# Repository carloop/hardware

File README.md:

# [Carloop](https://www.carloop.io)
## OBD-II CAN adapter for the Particle Photon/Electron and RedBear Duo

The WiFi-capable Particle Photon or better yet the cellular Particle
Electron can turn your car into a cloud connected device!

Carloop's PCB connects your car's CAN bus network to the Photon, Electron and Duo. It also provides battery power and a GPS to track location.

# Particle Photon Example

# [Check out the Carloop Store](https://store.carloop.io/)

## Features

* High-speed CAN transceiver [adapted from the OpenXC project](https://github.com/openxc/reference-vi/blob/gh-pages/electrical/design/can.mkd)
* Get power from the OBD-II port using [a robust circuit adapted from the OpenXC project](https://github.com/openxc/reference-vi/blob/gh-pages/electrical/design/power.mkd)
* GPS connector
* Stacked components for a more compact development kit than a
traditional 90-degrees PCB mount OBD-II connector.
* Powered by the Particle platform!

## Images

PCB

Assembled adapter

* [With Photon](images/detail-photon.jpg)
* [With Electron](images/detail-electron.jpg)
* [Front view](images/front.png)
* [Side view](images/detail-side.jpg)
* [Back view](images/back.png)
* [Angle view](images/angle.png)

## Hardware

There are a few hardware variants: [Carloop](Carloop.v2), [Carloop XL](CarloopXL.v3) and [Carloop Retro](CarloopRetro.v0).

Here are the PCB design files for the Revision 2.3, the one sold on the [Carloop store](https://store.carloop.io)

* [Schematic (PDF)](Carloop.v2/Carloop-v2.3.pdf)
  [(Eagle)](Carloop.v2/Carloop-v2.3.sch)
* [Layout](Carloop.v2/Carloop-v2.3-pcb-combined.pdf)
  [(top)](Carloop.v2/Carloop-v2.3-layout-top.pdf)
  [(bottom)](Carloop.v2/Carloop-v2.3-layout-bottom.pdf)
  [(Eagle)](Carloop.v2/Carloop-v2.3.brd)
* [Bill of materials](Carloop.v2/Carloop-v2.3_BOM.csv)
* [OSH Park order page](https://oshpark.com/shared_projects/ir8I9vT6)

Here are the PCB design files for the extended version that fits a Particle Electron. It is a prototype.

* [Schematic (Eagle)](CarloopXL.v3/Carloop-v3.1.sch)
* [Layout (Eagle)](CarloopXL.v3/Carloop-v3.1.brd)
* [Bill of materials](CarloopXL.v3/Carloop-v3.1_BOM.csv)

Here are the PCB design files for a "retro" variant with a K-Line transceiver contributed by [Alan R](https://github.com/cyclin-al).

* [Schematic (Eagle)](CarloopRetro.v0/CarloopRetro-v0.1.sch)
* [Layout (Eagle)](CarloopRetro.v0/CarloopRetro-v0.1.brd)

## Software

The [Carloop Library](https://github.com/carloop/carloop-library) is available on Particle's Web IDE.  You will need to flash a [Particle Photon](https://store.carloop.io/products/particle-photon), [Particle Electron](https://store.carloop.io/products/particle-electron) or [RedBear Duo](https://store.carloop.io/products/redbear-duo) with an example app which can ben found in Carloop Library.   See 'Getting Started' instructions here: [https://community.carloop.io/t/getting-started-with-carloop/23](https://community.carloop.io/t/getting-started-with-carloop/23)

## License

Copyright 2016 1000 Tools, Inc.

Licensed under the GPL v3

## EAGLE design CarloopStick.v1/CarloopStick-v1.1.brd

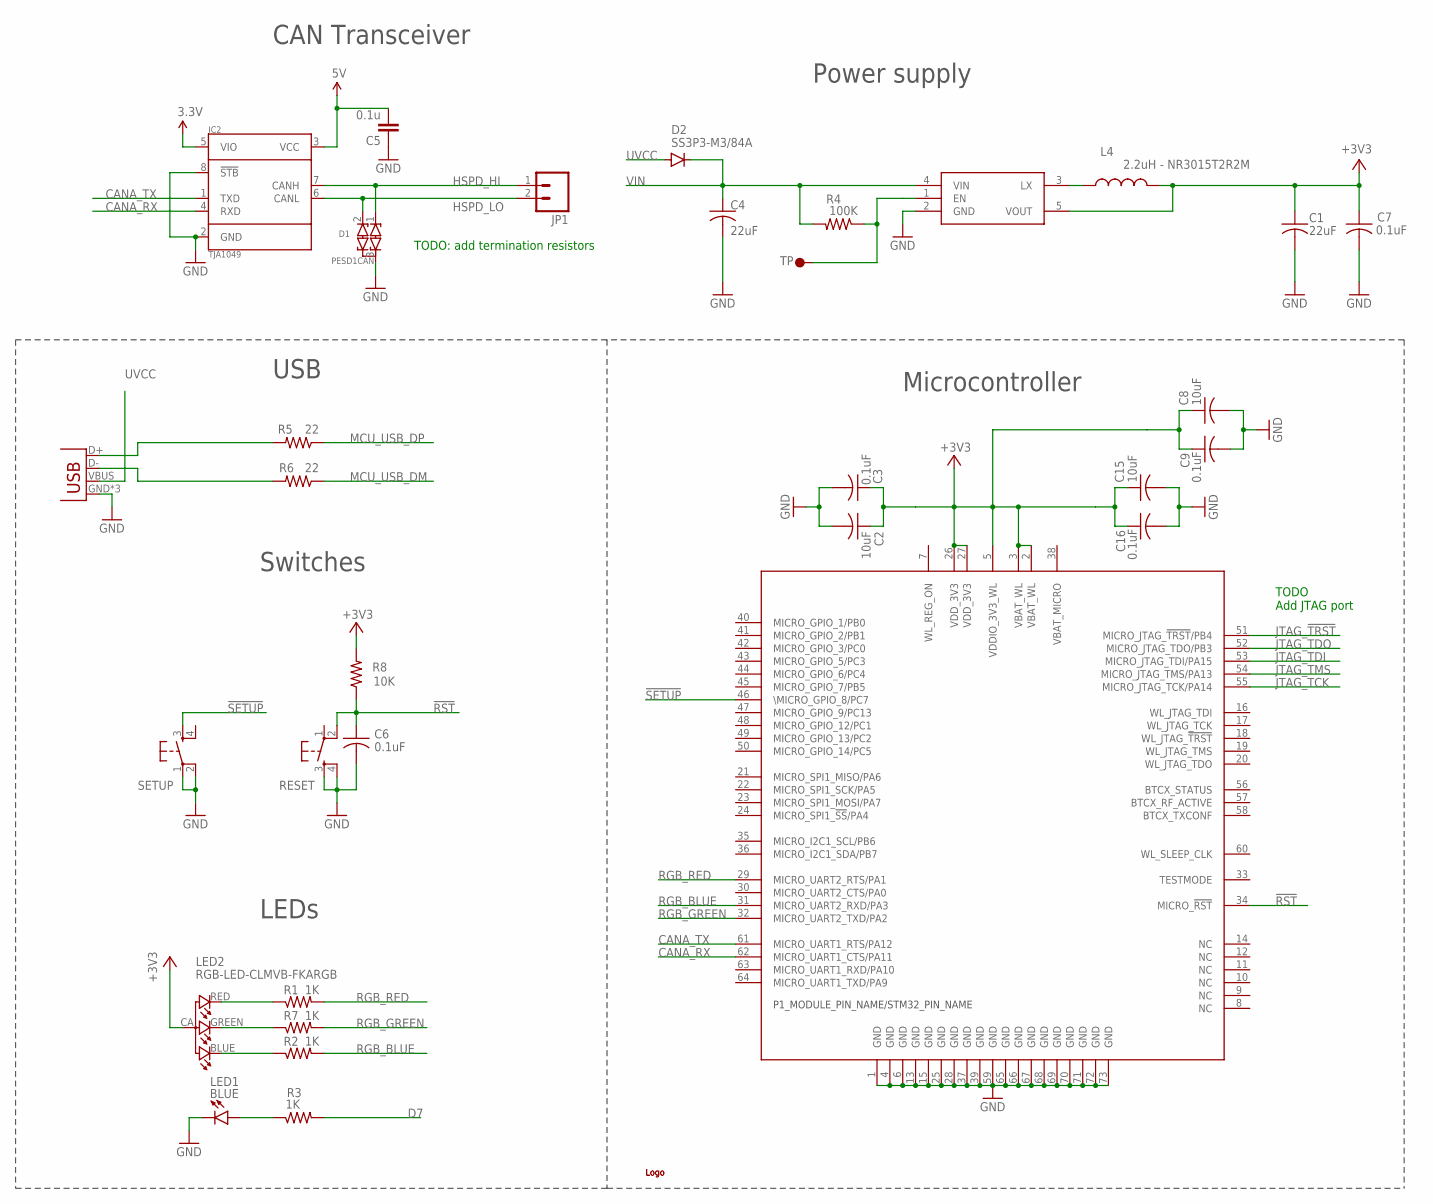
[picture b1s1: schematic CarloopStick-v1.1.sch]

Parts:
C1, C4: 22uF; C0603_B
C2, C8, C15: 10uF; C0603_B
C3, C6, C7, C9, C16: 0.1uF; C0402_B
C5: 0.1u; C0402; PARTNO GRM155R71C104KA88D
D1: PESD1CAN; SOT23; PARTNO PESD1CAN-215
D2: SS3P3-M3/84A; DIODE-DO-220AA(SMP)
IC2: TJA1049; SO8; PARTNO TJA1049T-118
JP1: M02PTH; 1X02
L4: 2.2uH - NR3015T2R2M; INDUCTOR-NR3015
LED2: RGB-LED-CLMVB-FKARGB; PLCC4-2MM-RGB
LED_USR: BLUE; LED-0603-NO-SS
R1, R2, R3, R7: 1K; R0402_B
R4: 100K; R0402_B
R5, R6: 22; R0402_B
R8: 10K; R0402_B
RESET: KMR211GLFS; TACTILE_SWITCH_SMD
SETUP: KMR211GLFS; TACTILE_SWITCH_SMD
U$1, U$5: LOGOSMALL; CARLOOP-2
U$4: P1; WM-N-BM-14
U$11: R8008-33; SOT23-5
U$12: TP3; TP60_BOT
X1: USB-MICROB; USB-MICROB-SLOT-HOLE

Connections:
3.3V: IC2.5 (VIO)
5V: C5.2, IC2.3 (VCC)
!RST: C6.1, R8.1, RESET.2, U$4.34 (MICRO_!RST!)
!SETUP: SETUP.3, U$4.46 (\MICRO_GPIO_8/PC7)
+3V3: C1.1, C2.1, C3.1, C7.1, C8.1, C9.1, C15.1, C16.1, L4.2, LED2.CA (1), R8.2, U$4.2 (VBAT_WL), U$4.3 (VBAT_WL), U$4.5 (VDDIO_3V3_WL), U$4.26 (VDD_3V3), U$4.27 (VDD_3V3), U$11.5 (VOUT)
CANA_RX: IC2.4 (RXD), U$4.62 (MICRO_UART1_CTS/PA11)
CANA_TX: IC2.1 (TXD), U$4.61 (MICRO_UART1_RTS/PA12)
D7: R3.2
GND: C1.2, C2.2, C3.2, C4.2, C5.1, C6.2, C7.2, C8.2, C9.2, C15.2, C16.2, D1.3 (COM), IC2.2 (GND), IC2.8 (!STB), LED_USR.C1 (C), RESET.3, RESET.4, SETUP.1, SETUP.2, U$4.1 (GND), U$4.4 (GND), U$4.6 (GND), U$4.13 (GND), U$4.15 (GND), U$4.25 (GND), U$4.28 (GND), U$4.37 (GND), U$4.39 (GND), U$4.59 (GND), U$4.65 (GND), U$4.66 (GND), U$4.67 (GND), U$4.68 (GND), U$4.69 (GND), U$4.70 (GND), U$4.71 (GND), U$4.72 (GND), U$4.73 (GND), U$11.2 (GND), X1.GND, X1.MT1 (GND), X1.MT2 (GND)
HSPD_HI: D1.1 (C1), IC2.7 (CANH), JP1.1
HSPD_LO: D1.2 (C2), IC2.6 (CANL), JP1.2
JTAG_!TRST: U$4.51 (MICRO_JTAG_!TRST!/PB4)
JTAG_TCK: U$4.55 (MICRO_JTAG_TCK/PA14)
JTAG_TDI: U$4.53 (MICRO_JTAG_TDI/PA15)
JTAG_TDO: U$4.52 (MICRO_JTAG_TDO/PB3)
JTAG_TMS: U$4.54 (MICRO_JTAG_TMS/PA13)
LED1: LED_USR.A1 (A), R3.1
MCU_USB_DM: R6.1
MCU_USB_DP: R5.1
unnamed: R5.2, X1.D+
unnamed: L4.1, U$11.3 (LX)
unnamed: R6.2, X1.D-
unnamed: R4.1, U$11.1 (EN), U$12.P$1
unnamed: LED2.BLUE (2), R2.1
unnamed: LED2.GREEN (3), R7.1
unnamed: LED2.RED (4), R1.1
RGB_BLUE: R2.2, U$4.31 (MICRO_UART2_RXD/PA3)
RGB_GREEN: R7.2, U$4.32 (MICRO_UART2_TXD/PA2)
RGB_RED: R1.2, U$4.29 (MICRO_UART2_RTS/PA1)
UVCC: D2.ANODE, X1.VBUS
VIN: C4.1, D2.CATHODE, R4.2, U$11.4 (VIN)

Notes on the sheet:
CAN Transceiver
USB
Microcontroller
Power supply
Switches
LEDs
TODO Add JTAG port
TODO: add termination resistors

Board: 2 copper layers, 34 parts (0 on the bottom side), 22 nets, no tracks yet.

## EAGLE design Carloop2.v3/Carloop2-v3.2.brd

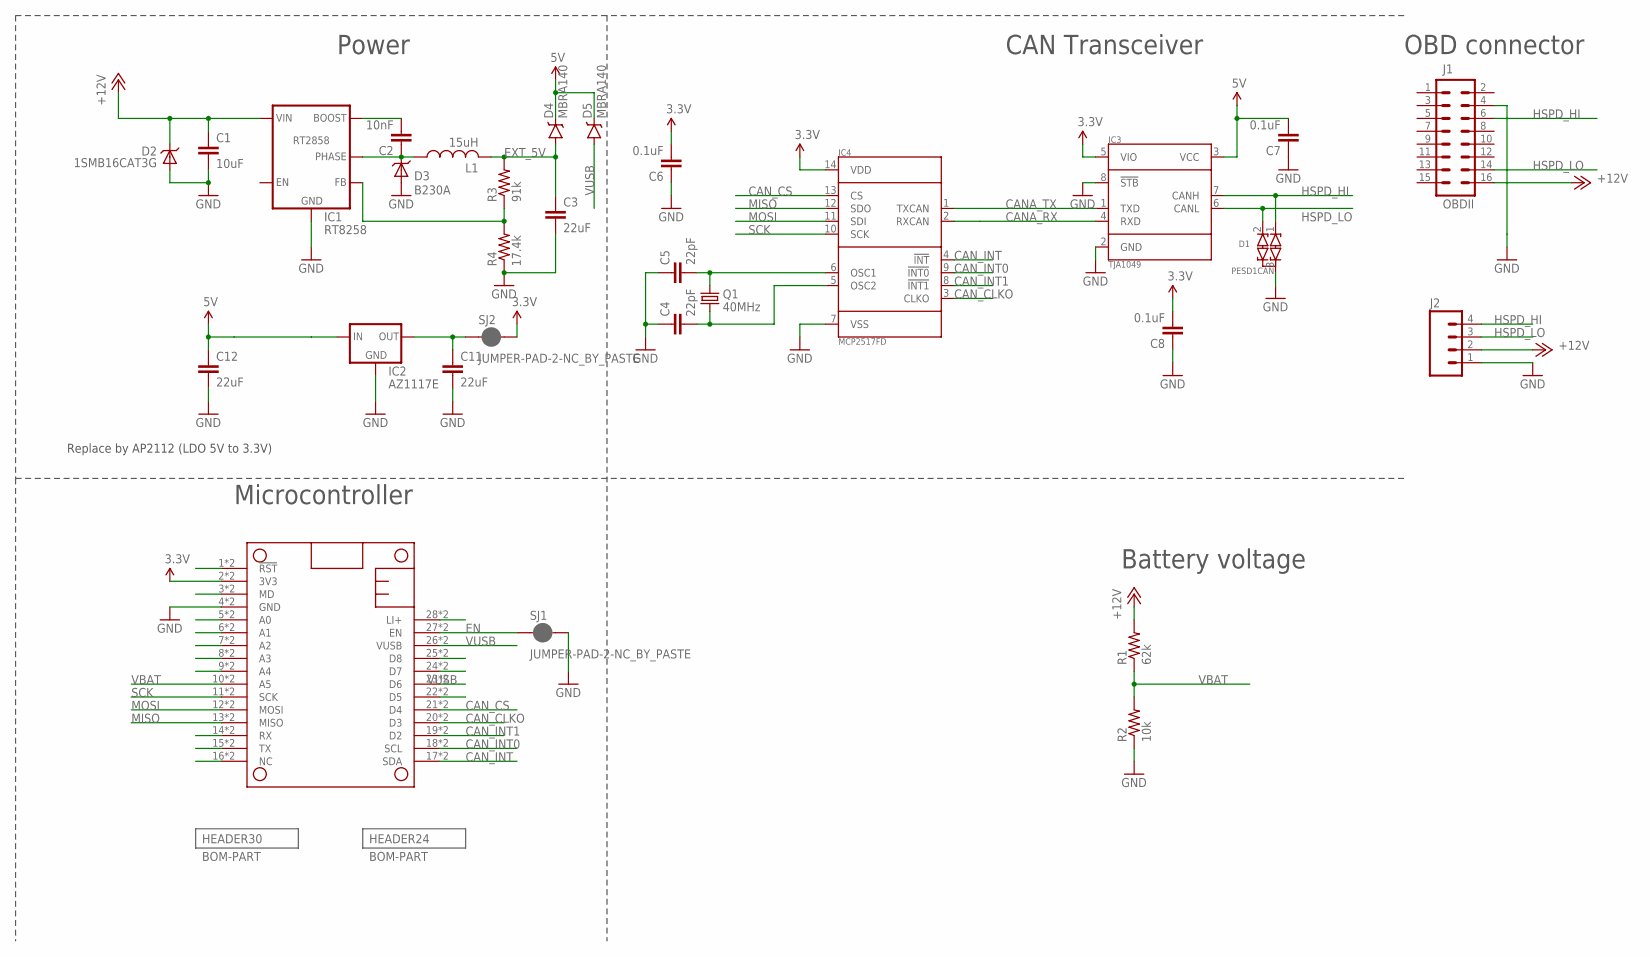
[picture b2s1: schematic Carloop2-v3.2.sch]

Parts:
C1: 10uF; C1206; PARTNO C3216X7R1E106K160AB
C2: 10nF; C0603; PARTNO CGA3E2X8R1H103K080AA
C3, C11, C12: 22uF; C1206; PARTNO CL31X226KAHN3NE
C4, C5: 22pF; C0603; PARTNO CC0603KRX7R9BB223
C6, C7, C8: 0.1uF; C0603; PARTNO CC0603JRX7R7BB104
D1: PESD1CAN; SOT23; PARTNO PESD1CAN-215
D2: 1SMB16CAT3G; SMB-DIODE; PARTNO 1SMB16CAT3G
D3: B230A; DO-214AA; PARTNO B230A-13-F
D4, D5: MBRA140; SMA-DIODE; PARTNO MBRA140T3G
IC1: RT8258; SOT-23-6; PARTNO RT8258GJ6
IC2: AZ1117E; SOT223; PARTNO AZ1117EH-3.3TRG1
IC3: TJA1049; SO8; PARTNO TJA1049T-118
IC4: MCP2517FD; SOIC-14; PARTNO MCP2517FD-H/SL
IC5: PARTICLE_MESH_SMTDUAL; FEATHERWING_SMT2
J1: OBDII; OBDII-COMTECH; PARTNO OBD-II
J2: M04SCREW; SCREWTERMINAL-3.5MM-4; PARTNO OSTTE040104
L1: 15uH; NR8040; PARTNO NR8040T150M
Q1: 40MHz; CRYSTAL-SMD-5X3; PARTNO ECS-400-12-30B-AGM-TR
R1: 62k; R0603; PARTNO ERA-3AEB623V
R2: 10k; R0603; PARTNO ERA-3AED103V
R3: 91k; R0603; PARTNO ERA-3ARB913V
R4: 17.4k; R0603; PARTNO ERJ-3EKF1742V
SJ1, SJ2: JUMPER-PAD-2-NC_BY_PASTE; PAD-JUMPER-2-NC_BY_PASTE_YES_SILK

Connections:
3.3V: C6.2, C8.2, IC3.5 (VIO), IC4.14 (VDD), IC5.2 (3V3), IC5.2' (3V3), SJ2.2
5V: C7.2, C12.1, D4.C, D5.C, IC2.3 (IN), IC3.3 (VCC)
+12V: C1.1, D2.C, IC1.5 (VIN), J1.16, J2.2, R1.2
BOOST\: C2.2, IC1.1 (BOOST)
CANA_RX: IC3.4 (RXD), IC4.2 (RXCAN)
CANA_TX: IC3.1 (TXD), IC4.1 (TXCAN)
CAN_CLKO: IC4.3 (CLKO), IC5.20 (D3), IC5.20' (D3)
CAN_CS: IC4.13 (CS), IC5.21 (D4), IC5.21' (D4)
CAN_INT: IC4.4 (!INT), IC5.17 (SDA), IC5.17' (SDA)
CAN_INT0: IC4.9 (!INT0), IC5.18 (SCL), IC5.18' (SCL)
CAN_INT1: IC4.8 (!INT1), IC5.19 (D2), IC5.19' (D2)
EN: IC5.27 (EN), IC5.27' (EN), SJ1.1
EXT_5V: C3.1, D4.A, L1.P$2 (2), R3.2
FB: IC1.3 (FB), R3.1, R4.2
GND: C1.2, C3.2, C4.1, C5.1, C6.1, C7.1, C8.1, C11.2, C12.2, D1.3 (COM), D2.A, D3.+ (A), IC1.2 (GND), IC2.1 (GND), IC2.4 (GND), IC3.2 (GND), IC3.8 (!STB), IC4.7 (VSS), IC5.4 (GND), IC5.4' (GND), J1.4, J2.1, R2.1, R4.1, SJ1.2
HSPD_HI: D1.1 (C1), IC3.7 (CANH), J1.6, J2.4
HSPD_LO: D1.2 (C2), IC3.6 (CANL), J1.14, J2.3
LI+: IC5.28 (LI+), IC5.28' (LI+)
MISO: IC4.12 (SDO), IC5.13 (MISO), IC5.13' (MISO)
MOSI: IC4.11 (SDI), IC5.12 (MOSI), IC5.12' (MOSI)
unnamed: C11.1, IC2.2 (OUT), SJ2.1
unnamed: C5.2, IC4.6 (OSC1), Q1.3 (2)
unnamed: IC5.1 (!RST), IC5.1' (!RST)
unnamed: IC5.3 (MD), IC5.3' (MD)
unnamed: IC5.5 (A0), IC5.5' (A0)
unnamed: IC5.6 (A1), IC5.6' (A1)
unnamed: IC5.7 (A2), IC5.7' (A2)
unnamed: IC5.8 (A3), IC5.8' (A3)
unnamed: IC5.9 (A4), IC5.9' (A4)
unnamed: IC5.25 (D8), IC5.25' (D8)
unnamed: IC5.24 (D7), IC5.24' (D7)
unnamed: IC5.23 (D6), IC5.23' (D6)
unnamed: IC5.22 (D5), IC5.22' (D5)
unnamed: IC5.14 (RX), IC5.14' (RX)
unnamed: IC5.15 (TX), IC5.15' (TX)
unnamed: IC5.16 (NC), IC5.16' (NC)
unnamed: C4.2, IC4.5 (OSC2), Q1.1
PHASE: C2.1, D3.- (C), IC1.6 (PHASE), L1.P$1 (1)
SCK: IC4.10 (SCK), IC5.11 (SCK), IC5.11' (SCK)
VBAT: IC5.10 (A5), IC5.10' (A5), R1.1, R2.2
VUSB: D5.A, IC5.26 (VUSB), IC5.26' (VUSB)

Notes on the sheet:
Power
Battery voltage
OBD connector
Microcontroller
CAN Transceiver
Replace by AP2112 (LDO 5V to 3.3V)

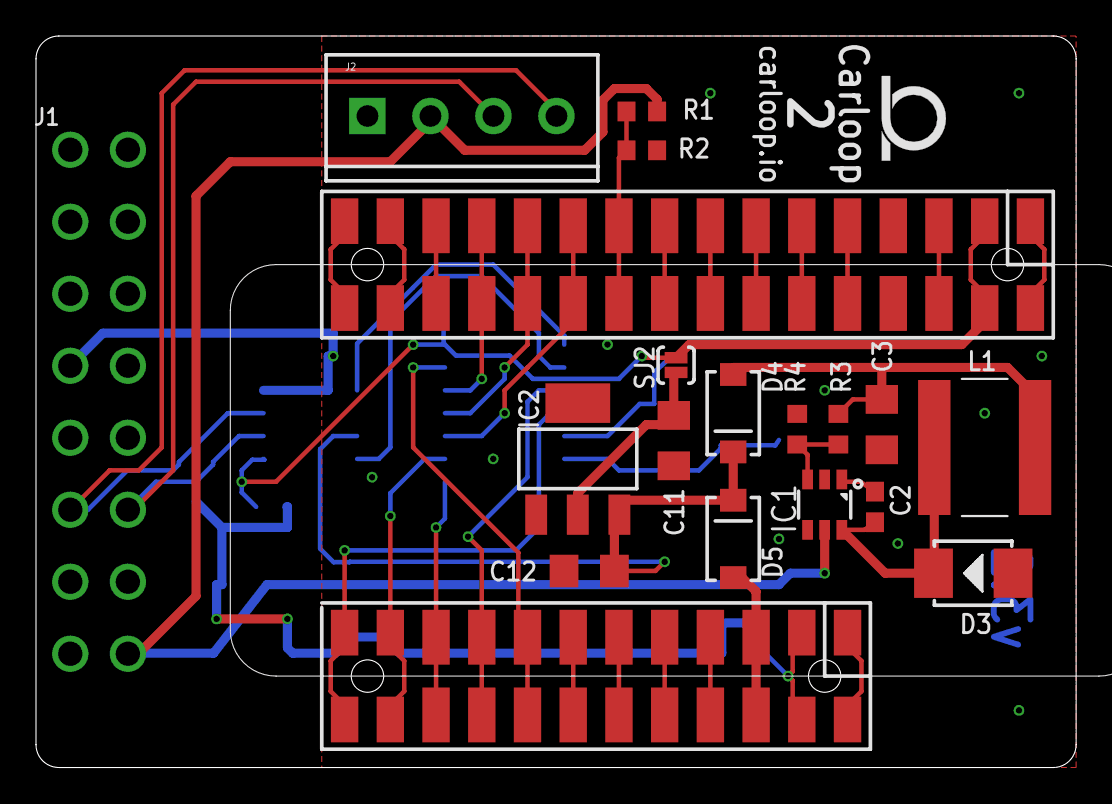
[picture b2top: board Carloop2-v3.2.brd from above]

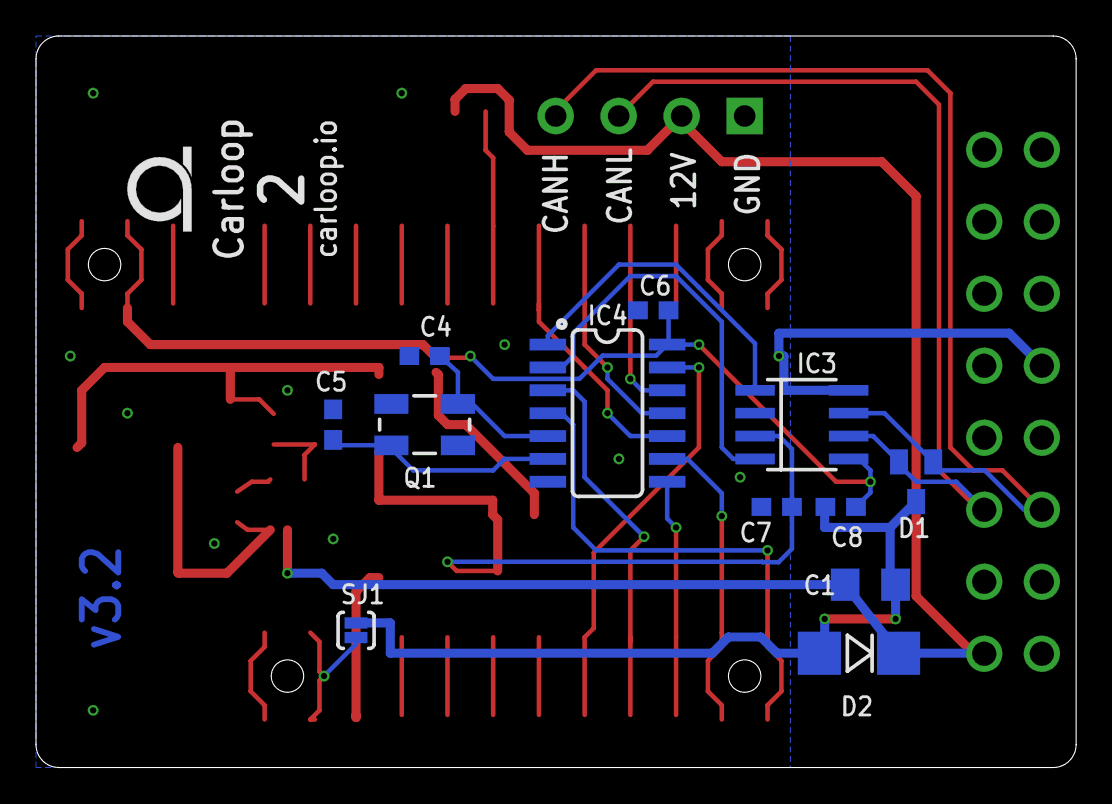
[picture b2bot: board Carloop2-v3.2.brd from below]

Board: 2 copper layers, 57.8 x 40.6 mm, 32 parts (13 on the bottom side), 41 nets.

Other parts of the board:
U$3, U$5: LOGOSMALL; CARLOOP-2

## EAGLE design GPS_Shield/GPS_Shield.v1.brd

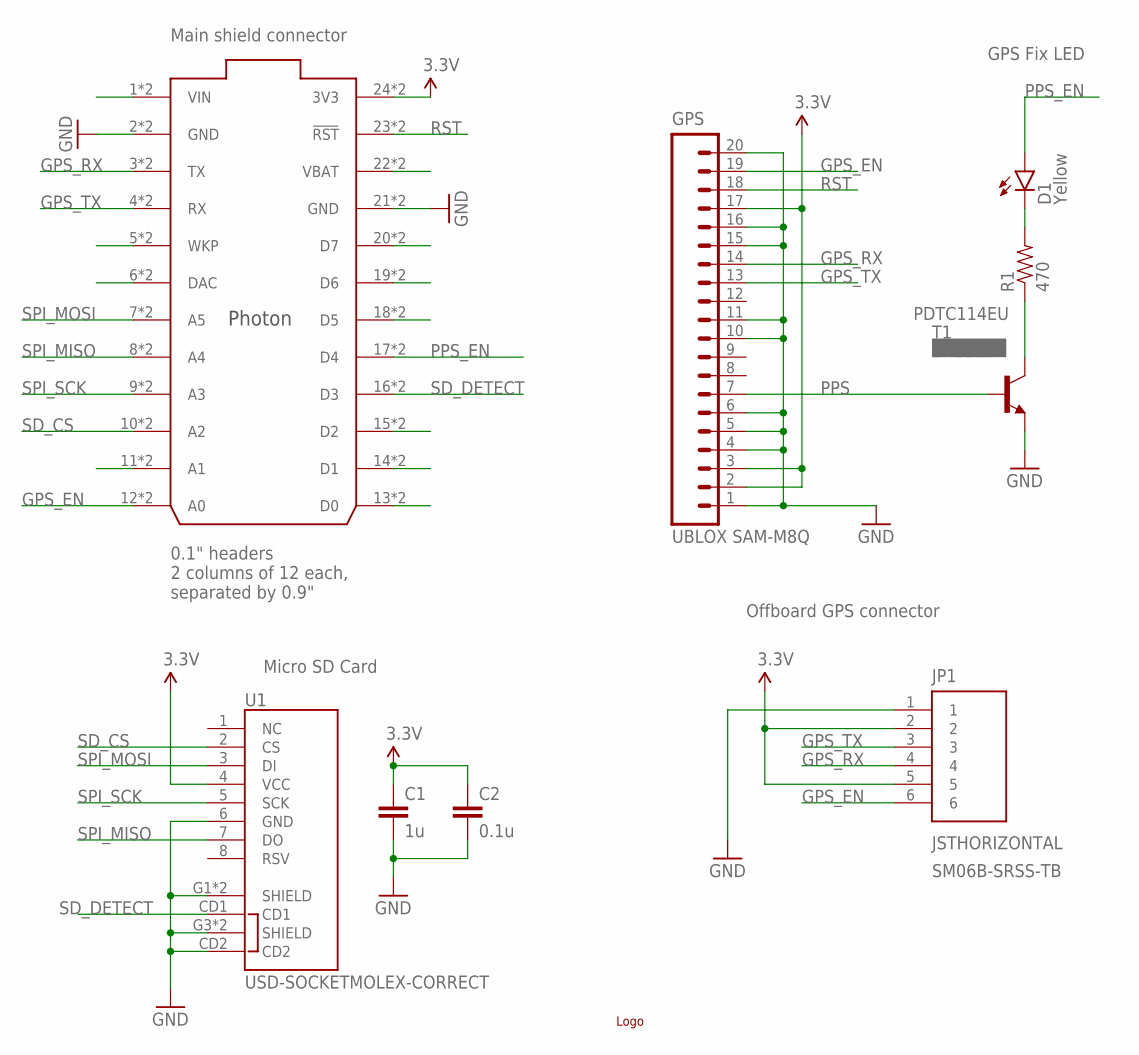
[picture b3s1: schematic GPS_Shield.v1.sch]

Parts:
C1: 1u; 0603-CAP
C2: 0.1u; 0603-CAP
CORE: PHOTONWITH_EXTERNAL_HEADERS; PHOTON_STACKABLE_EXTERNAL; PARTNO *
D1: Yellow; LED-0603
GPS: UBLOX SAM-M8Q; 1X20
JP1: JSTHORIZONTAL; JST-6-SMD-HOR-1.0MM; PARTNO SM06B-SRSS-TB
R1: 470; 0603-RES
T1: 2N2222; TO18
U1: USD-SOCKETMOLEX-CORRECT; MICRO-SD-MOLEX-CORRECT
U$1: LOGO; CARLOOP

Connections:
3.3V: C1.1, C2.1, CORE.24 (3V3), CORE.@24 (3V3), GPS.2, GPS.3, GPS.17, JP1.2, JP1.5, U1.4 (VCC)
CANA_EN: CORE.13 (D0), CORE.@13 (D0)
CANA_RX: CORE.15 (D2), CORE.@15 (D2)
CANA_TX: CORE.14 (D1), CORE.@14 (D1)
GND: C1.2, C2.2, CORE.2 (GND), CORE.21 (GND), CORE.@2 (GND), CORE.@21 (GND), GPS.1, GPS.4, GPS.5, GPS.6, GPS.10, GPS.11, GPS.15, GPS.16, GPS.20, JP1.1, T1.1 (E), U1.6 (GND), U1.CD2, U1.G1 (SHIELD), U1.G2 (SHIELD), U1.G3 (SHIELD), U1.G4 (SHIELD)
GPS_EN: CORE.12 (A0), CORE.@12 (A0), GPS.19, JP1.6
GPS_RX: CORE.3 (TX), CORE.@3 (TX), GPS.14, JP1.4
GPS_TX: CORE.4 (RX), CORE.@4 (RX), GPS.13, JP1.3
unnamed: R1.1, T1.3 (C)
unnamed: D1.C, R1.2
unnamed: CORE.6 (DAC), CORE.@6 (DAC)
unnamed: CORE.22 (VBAT), CORE.@22 (VBAT)
unnamed: CORE.20 (D7), CORE.@20 (D7)
unnamed: CORE.19 (D6), CORE.@19 (D6)
unnamed: CORE.1 (VIN), CORE.@1 (VIN)
unnamed: CORE.5 (WKP), CORE.@5 (WKP)
PPS: GPS.7, T1.2 (B)
PPS_EN: CORE.17 (D4), CORE.18 (D5), CORE.@17 (D4), CORE.@18 (D5), D1.A
RST: CORE.23 (!RST), CORE.@23 (!RST), GPS.18
SD_CS: CORE.10 (A2), CORE.@10 (A2), U1.2 (CS)
SD_DETECT: CORE.16 (D3), CORE.@16 (D3), U1.CD1
SPI_MISO: CORE.8 (A4), CORE.@8 (A4), U1.7 (DO)
SPI_MOSI: CORE.7 (A5), CORE.@7 (A5), U1.3 (DI)
SPI_SCK: CORE.9 (A3), CORE.@9 (A3), U1.5 (SCK)
VBAT: CORE.11 (A1), CORE.@11 (A1)

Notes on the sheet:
PDTC114EU
SM06B-SRSS-TB
Offboard GPS connector
0.1" headers 2 columns of 12 each, separated by 0.9"
Main shield connector
GPS Fix LED
Micro SD Card

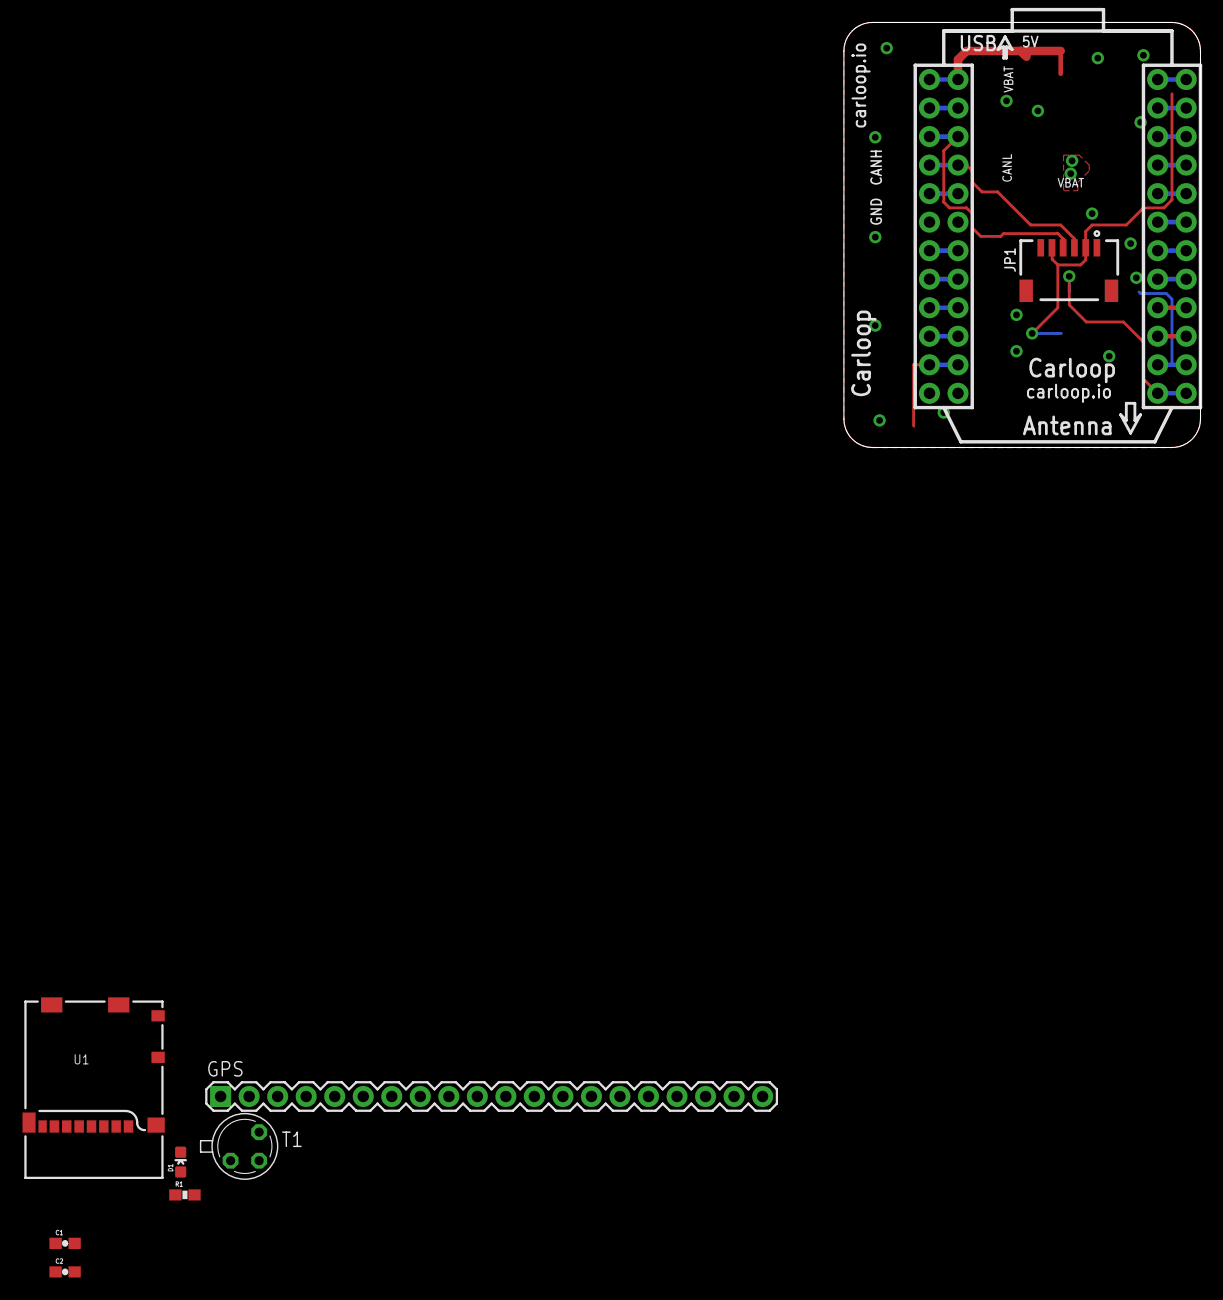
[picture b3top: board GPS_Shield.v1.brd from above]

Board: 2 copper layers, 31.8 x 37.8 mm, 12 parts (1 on the bottom side), 25 nets.

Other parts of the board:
F2: OSHW-LOGO-S
ZDRAW1: A4L-LOC

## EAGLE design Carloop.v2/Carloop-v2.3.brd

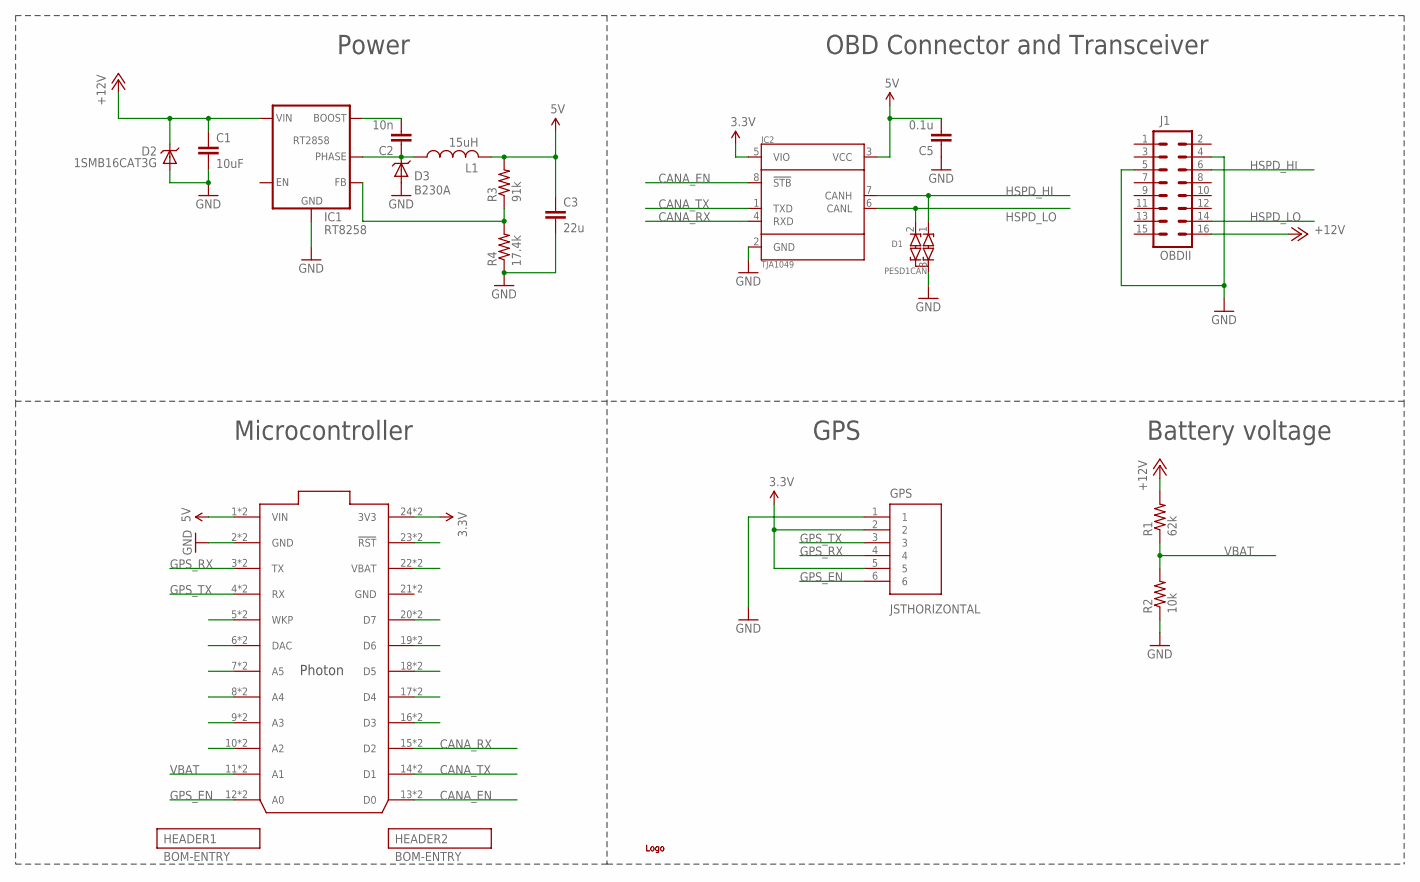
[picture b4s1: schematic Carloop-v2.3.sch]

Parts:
C1: 10uF; C1206; PARTNO GRM31CR61E106KA12L
C2: 10n; C0402; PARTNO C0402C103K5RACTU
C3: 22u; C1206; PARTNO GRM31CR61C226ME15L
C5: 0.1u; C0402; PARTNO GRM155R71C104KA88D
CORE: PHOTONWITH_EXTERNAL_HEADERS; PHOTON_STACKABLE_EXTERNAL; PARTNO *
D1: PESD1CAN; SOT23; PARTNO PESD1CAN-215
D2: 1SMB16CAT3G; SMB-DIODE; PARTNO 1SMB16CAT3G
D3: B230A; DO-214AA; PARTNO B230A-13-F
GPS: JSTHORIZONTAL; JST-6-SMD-HOR-1.0MM; PARTNO SM06B-SRSS-TB
IC1: RT8258; SOT-23-6; PARTNO RT8258GJ6
IC2: TJA1049; SO8; PARTNO TJA1049T-118
J1: OBDII; OBDII-STRAIGHT; PARTNO OBD-II
L1: 15uH; NR8040; PARTNO NR8040T150M
R1: 62k; R0402; PARTNO ERJ-2RKF6202X
R2: 10k; R0402; PARTNO ERJ-2RKF1002X
R3: 91k; R0402; PARTNO ERJ-2RKF9102X
R4: 17.4k; R0402; PARTNO ERJ-2RKF1742X
U$1, U$5: LOGOSMALL; CARLOOP-2

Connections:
3.3V: CORE.24 (3V3), CORE.@24 (3V3), GPS.2, GPS.5, IC2.5 (VIO)
5V: C3.1, C5.2, CORE.1 (VIN), CORE.@1 (VIN), IC2.3 (VCC), L1.P$2 (2), R3.2
+12V: C1.1, D2.C, IC1.5 (VIN), J1.16, R1.2
CANA_EN: CORE.13 (D0), CORE.@13 (D0), IC2.8 (!STB)
CANA_RX: CORE.15 (D2), CORE.@15 (D2), IC2.4 (RXD)
CANA_TX: CORE.14 (D1), CORE.@14 (D1), IC2.1 (TXD)
GND: C1.2, C3.2, C5.1, CORE.2 (GND), CORE.21 (GND), CORE.@2 (GND), CORE.@21 (GND), D1.3 (COM), D2.A, D3.+ (A), GPS.1, IC1.2 (GND), IC2.2 (GND), J1.4, J1.5, R2.1, R4.1
GPS_EN: CORE.12 (A0), CORE.@12 (A0), GPS.6
GPS_RX: CORE.3 (TX), CORE.@3 (TX), GPS.4
GPS_TX: CORE.4 (RX), CORE.@4 (RX), GPS.3
HSPD_HI: D1.1 (C1), IC2.7 (CANH), J1.6
HSPD_LO: D1.2 (C2), IC2.6 (CANL), J1.14
unnamed: C2.1, D3.- (C), IC1.6 (PHASE), L1.P$1 (1)
unnamed: C2.2, IC1.1 (BOOST)
unnamed: CORE.23 (!RST), CORE.@23 (!RST)
unnamed: CORE.22 (VBAT), CORE.@22 (VBAT)
unnamed: CORE.20 (D7), CORE.@20 (D7)
unnamed: CORE.19 (D6), CORE.@19 (D6)
unnamed: CORE.18 (D5), CORE.@18 (D5)
unnamed: CORE.17 (D4), CORE.@17 (D4)
unnamed: CORE.16 (D3), CORE.@16 (D3)
unnamed: IC1.3 (FB), R3.1, R4.2
unnamed: CORE.10 (A2), CORE.@10 (A2)
unnamed: CORE.9 (A3), CORE.@9 (A3)
unnamed: CORE.8 (A4), CORE.@8 (A4)
unnamed: CORE.7 (A5), CORE.@7 (A5)
unnamed: CORE.6 (DAC), CORE.@6 (DAC)
unnamed: CORE.5 (WKP), CORE.@5 (WKP)
VBAT: CORE.11 (A1), CORE.@11 (A1), R1.1, R2.2

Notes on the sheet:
OBD Connector and Transceiver
Power
Microcontroller
GPS
Battery voltage

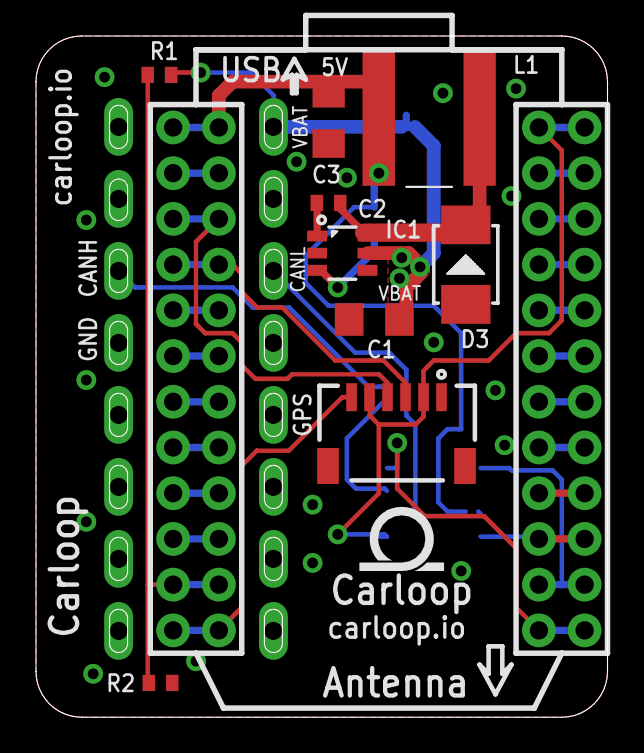
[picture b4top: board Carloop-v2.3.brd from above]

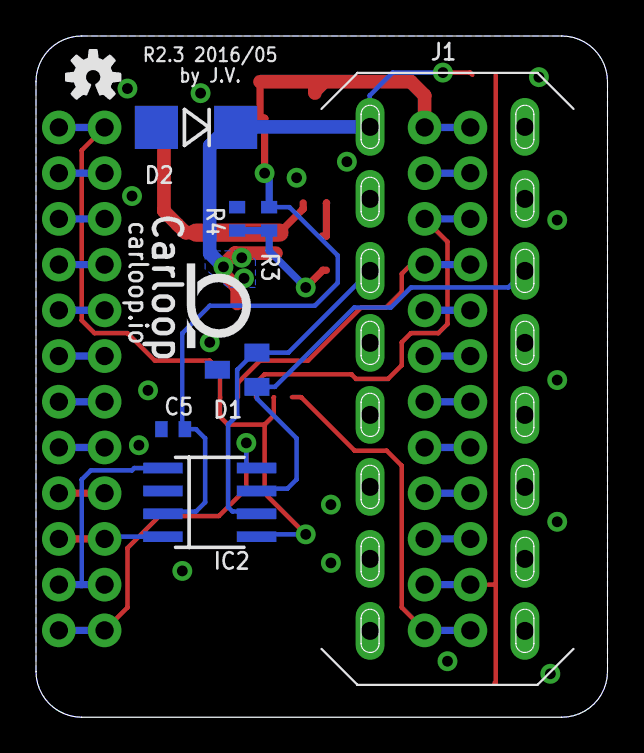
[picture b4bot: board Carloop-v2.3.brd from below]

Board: 2 copper layers, 31.8 x 37.8 mm, 21 parts (9 on the bottom side), 29 nets.

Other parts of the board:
F2: OSHW-LOGO-S
ZDRAW1: A4L-LOC

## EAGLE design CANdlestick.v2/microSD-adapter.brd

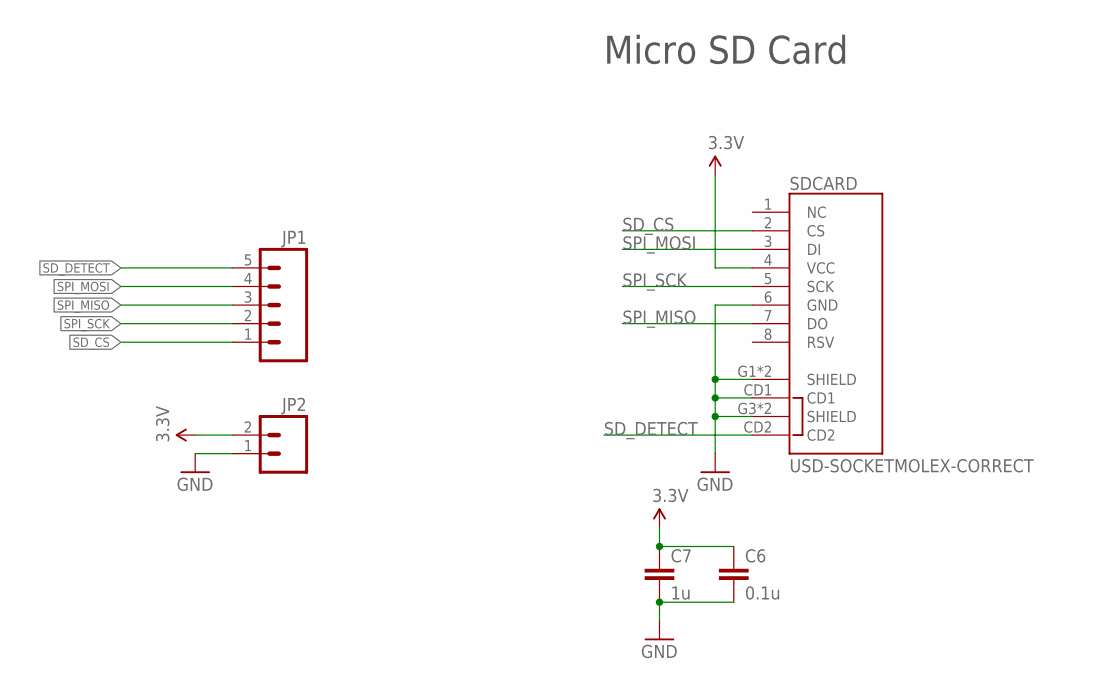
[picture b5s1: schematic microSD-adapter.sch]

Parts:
C6: 0.1u; C0805; PARTNO 08055C104KAT2A
C7: 1u; C0805; PARTNO CC0805KKX7R7BB105
JP1: M05PTH; 1X05
JP2: M02PTH; 1X02
SDCARD: USD-SOCKETMOLEX-CORRECT; MICRO-SD-MOLEX-CORRECT; PARTNO 1040310811

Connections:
3.3V: C6.1, C7.1, JP2.2, SDCARD.4 (VCC)
GND: C6.2, C7.2, JP2.1, SDCARD.6 (GND), SDCARD.CD1, SDCARD.G1 (SHIELD), SDCARD.G2 (SHIELD), SDCARD.G3 (SHIELD), SDCARD.G4 (SHIELD)
SD_CS: JP1.1, SDCARD.2 (CS)
SD_DETECT: JP1.5, SDCARD.CD2
SPI_MISO: JP1.3, SDCARD.7 (DO)
SPI_MOSI: JP1.4, SDCARD.3 (DI)
SPI_SCK: JP1.2, SDCARD.5 (SCK)

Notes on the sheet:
Micro SD Card

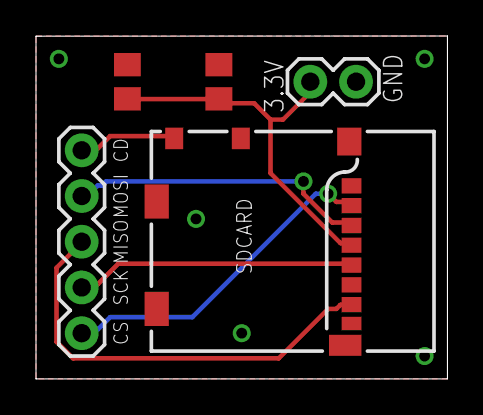
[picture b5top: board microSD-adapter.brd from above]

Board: 2 copper layers, 22.9 x 19.1 mm, 5 parts (0 on the bottom side), 7 nets.

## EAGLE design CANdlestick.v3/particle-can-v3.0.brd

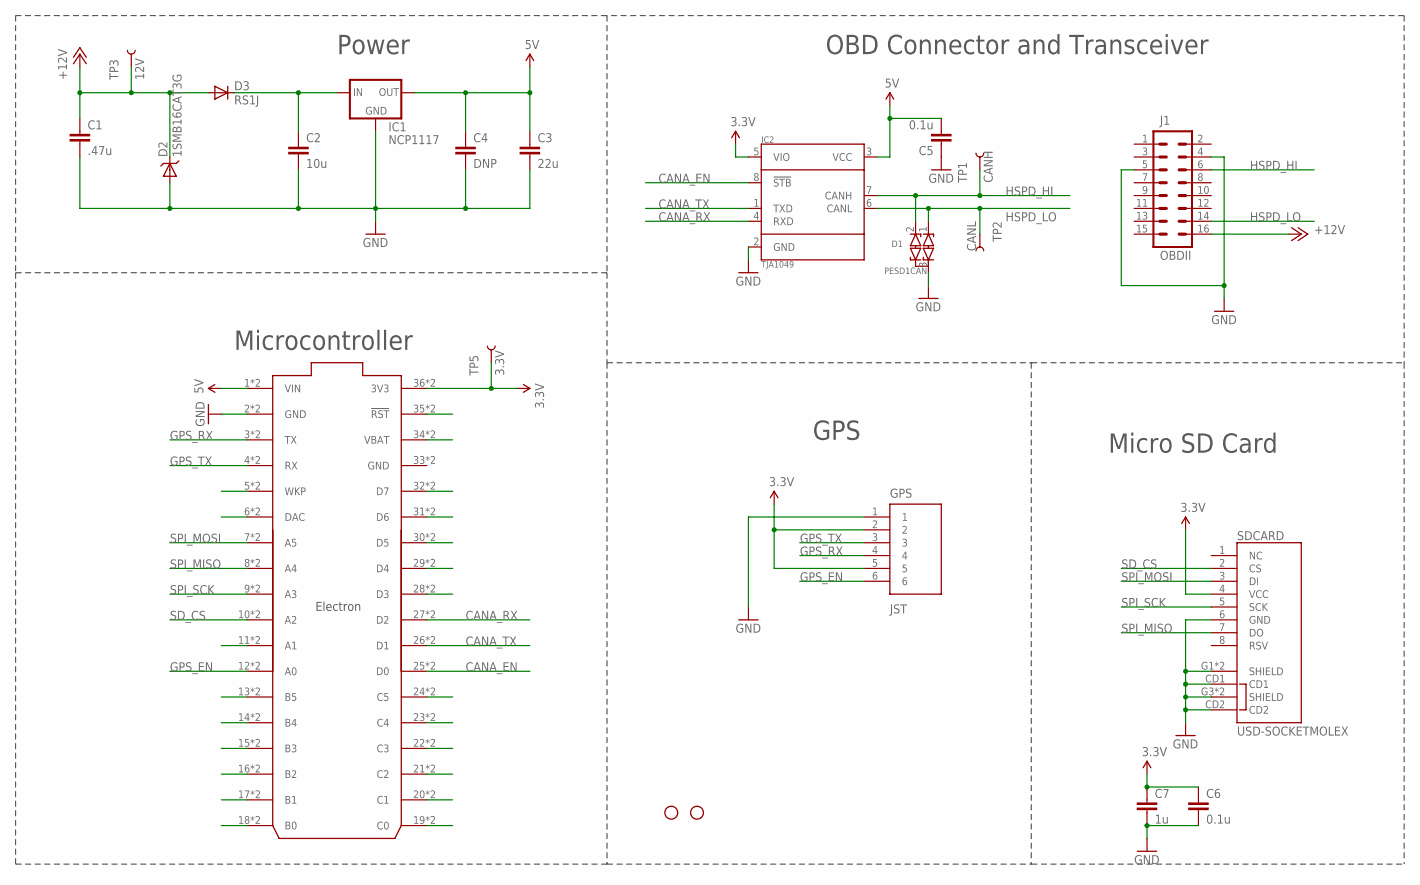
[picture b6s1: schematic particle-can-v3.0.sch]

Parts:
C1: .47u; C0805; PARTNO C0805C474K5RACTU
C2: 10u; C0805; PARTNO GRM21BR6YA106KE43L
C3: 22u; C0805; PARTNO GRM219R61A226MEA0D
C4: DNP; C0805; PARTNO GRM219R61A226MEA0D
C5, C6: 0.1u; C0805; PARTNO 08055C104KAT2A
C7: 1u; C0805; PARTNO CC0805KKX7R7BB105
D1: PESD1CAN; SOT23; PARTNO PESD1CAN-215
D2: 1SMB16CAT3G; SMB-DIODE; PARTNO 1SMB16CAT3G
D3: RS1J; SMA-DIODE; PARTNO RS1J-E3/5AT
ELECTRON: ELECTRON_WITH_EXTERNAL_HEADERS; ELECTRON_EXTERNAL; PARTNO PPTC181LFBN-RC
GPS: JST; JST-6-SMD-VERT-1.0MM; PARTNO BM06B-SRSS-TB
IC1: NCP1117; SOT223; PARTNO NCP1117LPST50T3G
IC2: TJA1049; SO8; PARTNO TJA1049T-118
J1: OBDII; OBDII-COMTECH; PARTNO OBD-II
SDCARD: USD-SOCKETMOLEX; MICRO-SD-MOLEX; PARTNO 1040310811
STANDOFF1, STANDOFF2: STAND-OFF
TP1: CANH; PAD.03X.03
TP2: CANL; PAD.03X.03
TP3: 12V; PAD.03X.03
TP5: 3.3V; PAD.03X.03

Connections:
3.3V: C6.1, C7.1, ELECTRON.36 (3V3), ELECTRON.@36 (3V3), GPS.2, GPS.5, IC2.5 (VIO), SDCARD.4 (VCC), TP5.P$1
5V: C3.1, C4.1, C5.2, ELECTRON.1 (VIN), ELECTRON.@1 (VIN), IC1.3 (OUT), IC1.4 (OUT), IC2.3 (VCC)
+12V: C1.1, D2.C, D3.A, J1.16, TP3.P$1
CANA_EN: ELECTRON.25 (D0), ELECTRON.@25 (D0), IC2.8 (!STB)
CANA_RX: ELECTRON.27 (D2), ELECTRON.@27 (D2), IC2.4 (RXD)
CANA_TX: ELECTRON.26 (D1), ELECTRON.@26 (D1), IC2.1 (TXD)
GND: C1.2, C2.2, C3.2, C4.2, C5.1, C6.2, C7.2, D1.3 (COM), D2.A, ELECTRON.2 (GND), ELECTRON.33 (GND), ELECTRON.@2 (GND), ELECTRON.@33 (GND), GPS.1, IC1.1 (GND), IC2.2 (GND), J1.4, J1.5, SDCARD.6 (GND), SDCARD.CD1, SDCARD.CD2, SDCARD.G1 (SHIELD), SDCARD.G2 (SHIELD), SDCARD.G3 (SHIELD), SDCARD.G4 (SHIELD)
GPS_EN: ELECTRON.12 (A0), ELECTRON.@12 (A0), GPS.6
GPS_RX: ELECTRON.3 (TX), ELECTRON.@3 (TX), GPS.4
GPS_TX: ELECTRON.4 (RX), ELECTRON.@4 (RX), GPS.3
HSPD_HI: D1.2 (C2), IC2.7 (CANH), J1.6, TP1.P$1
HSPD_LO: D1.1 (C1), IC2.6 (CANL), J1.14, TP2.P$1
unnamed: ELECTRON.13 (B5), ELECTRON.@13 (B5)
unnamed: ELECTRON.14 (B4), ELECTRON.@14 (B4)
unnamed: ELECTRON.35 (!RST), ELECTRON.@35 (!RST)
unnamed: ELECTRON.34 (VBAT), ELECTRON.@34 (VBAT)
unnamed: ELECTRON.32 (D7), ELECTRON.@32 (D7)
unnamed: ELECTRON.31 (D6), ELECTRON.@31 (D6)
unnamed: ELECTRON.30 (D5), ELECTRON.@30 (D5)
unnamed: ELECTRON.29 (D4), ELECTRON.@29 (D4)
unnamed: ELECTRON.28 (D3), ELECTRON.@28 (D3)
unnamed: ELECTRON.15 (B3), ELECTRON.@15 (B3)
unnamed: ELECTRON.11 (A1), ELECTRON.@11 (A1)
unnamed: ELECTRON.16 (B2), ELECTRON.@16 (B2)
unnamed: ELECTRON.17 (B1), ELECTRON.@17 (B1)
unnamed: ELECTRON.18 (B0), ELECTRON.@18 (B0)
unnamed: ELECTRON.19 (C0), ELECTRON.@19 (C0)
unnamed: ELECTRON.20 (C1), ELECTRON.@20 (C1)
unnamed: ELECTRON.21 (C2), ELECTRON.@21 (C2)
unnamed: ELECTRON.6 (DAC), ELECTRON.@6 (DAC)
unnamed: ELECTRON.5 (WKP), ELECTRON.@5 (WKP)
unnamed: ELECTRON.23 (C4), ELECTRON.@23 (C4)
unnamed: ELECTRON.24 (C5), ELECTRON.@24 (C5)
unnamed: ELECTRON.22 (C3), ELECTRON.@22 (C3)
unnamed: C2.1, D3.C, IC1.2 (IN)
SD_CS: ELECTRON.10 (A2), ELECTRON.@10 (A2), SDCARD.2 (CS)
SPI_MISO: ELECTRON.8 (A4), ELECTRON.@8 (A4), SDCARD.7 (DO)
SPI_MOSI: ELECTRON.7 (A5), ELECTRON.@7 (A5), SDCARD.3 (DI)
SPI_SCK: ELECTRON.9 (A3), ELECTRON.@9 (A3), SDCARD.5 (SCK)

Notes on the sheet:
OBD Connector and Transceiver
Power
Microcontroller
GPS
Micro SD Card

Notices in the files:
parts and their libraries:
SparkFun-Connectors: Licensing: Creative Commons ShareAlike 4.0 International - https://creativecommons.org/licenses/by-sa/4.0
SparkFun-Aesthetics: Licensing: CC v3.0 Share-Alike You are welcome to use this library for commercial purposes.
bom: Copyright (C) 2010, Bob Starr
